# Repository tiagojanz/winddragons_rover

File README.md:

# WindDragons — Sistema de Telemetria e Controlo Náutico (Rover & Base Station)

Projeto de automação, navegação autónoma e telemetria para boias robóticas de regata (**Rovers**) e estação de comando com ecrã (**Base Station**), baseado na **Placa Carrier Universal Dual ESP32-C6** (**Master Lafvin LCD 1.47" IPS** + **Coprocessador ESP32-C6 DevKitC-1**).

---

## 🛰️ 1. Arquitetura Global do Sistema

```mermaid
flowchart LR
  subgraph CLOUD["☁️ WindDragons Cloud"]
    API["HTTPS REST API<br/>/api/circuits/station/telemetry"]
  end

  subgraph BASE["🎮 BASE STATION - Dual ESP32-C6"]
    BM["Master: Lafvin ESP32-C6<br/>• LCD 1.47 pol. ST7789 320x172<br/>• MicroSD /www/base/<br/>• Web Server WiFi STA e AP<br/>• Joystick Analógico + Botões<br/>• Coordenador OTA Dual"]
    BC["Slave: ESP32-C6 DevKitC-1<br/>• Rádio LoRa SX1278 433 MHz<br/>• Polling e Escuta Contínua<br/>• Telemetria da Frota 1..8"]
    BM <-->|"UART Inter-ESP 115200 bps<br/>TX:IO2 / RX:IO1"| BC
  end

  subgraph ROVER["🚤 ROVER / BOIA AUTÓNOMA - Dual ESP32-C6"]
    RM["Master: Lafvin ESP32-C6<br/>• LCD 1.47 pol. ST7789 + MicroSD<br/>• GPS Quectel LC29H UART1<br/>• Dashboard Web e OTA Dual<br/>• Joystick Local Opcional"]
    RC["Slave: ESP32-C6 DevKitC-1<br/>• Rádio LoRa SX1278 433 MHz<br/>• IMU 9-DOF GY-BNO055 em J_EXP<br/>• PWM: ESC, Leme, Guincho, Trinco<br/>• Sensores: Bateria 6S, Hall, Fim-Curso<br/>• Fita LEDs WS2812B Strobe"]
    RM <-->|"UART Inter-ESP 115200 bps<br/>TX:IO2 / RX:IO1"| RC
  end

  BM <-->|"WiFi HTTPS JSON"| API
  BC <-->|"LoRa 433 MHz<br/>BW 250kHz • SF7"| RC
```

---

## 🧭 2. Esquema de Ligação — Bússola & IMU 9-DOF (`GY-BNO055` em `J_EXP`)

O módulo **GY-BNO055** liga-se diretamente à ilha de expansão **`J_EXP` (2x03 pinos, passo 2.54 mm)** da PCB Carrier (ligada ao **Coprocessador ESP32-C6 DevKitC-1**).

```mermaid
flowchart LR
  subgraph J_EXP["📌 Conector J_EXP - PCB Carrier C6"]
    direction TB
    P1["Pino 1: IO1 - GPIO 1<br/>Coluna Esq. Topo"]
    P3["Pino 3: IO11 - GPIO 11<br/>Coluna Esq. Meio"]
    P5["Pino 5: GND<br/>Coluna Esq. Base"]
    P2["Pino 2: 3V3 - +3.3V_C6<br/>Coluna Dir. Topo"]
    P4["Pino 4: 5V<br/>Não ligar ao BNO055"]
    P6["Pino 6: GND<br/>Coluna Dir. Base"]
  end

  subgraph BNO["🧭 Módulo GY-BNO055 - I2C 0x28"]
    direction TB
    VIN["VIN - Alimentação 3.3V"]
    GND["GND - Terra Comum"]
    SCL["SCL / Rx - I2C Clock"]
    SDA["SDA / Tx - I2C Data"]
    ADD["ADD - Aberto = 0x28"]
    INT["INT / BOOT / REST - NC"]
  end

  P2 -->|"🔴 Fio Vermelho +3.3V"| VIN
  P5 -->|"⚫ Fio Preto GND"| GND
  P3 -->|"🟡 Fio Amarelo I2C SCL"| SCL
  P1 <-->|"🔵 Fio Azul/Verde I2C SDA"| SDA
```

### Disposição Física da Serigrafia `J_EXP` na PCB vs `GY-BNO055`

```text
       PCB CARRIER — ILHA J_EXP                     MÓDULO GY-BNO055
    ┌────────────────────────────┐               ┌────────────────────┐
    │     Col. Esq.    Col. Dir. │               │  [o] VIN     <────────── Pino 2 (3V3)
    │                            │               │  [o] GND     <────────── Pino 5 ou 6 (GND)
    │     [■] IO1      [●] 3V3   │ ──(Pinos 1,2) │  [o] SCL\Rx  <────────── Pino 3 (IO11)
    │     [●] IO11     [●] 5V    │ ──(Pinos 3,4) │  [o] SDA\Tx  <────────── Pino 1 (IO1)
    │     [●] GND      [●] GND   │ ──(Pinos 5,6) │  [o] ADD     (NC = 0x28)
    │         EXPANSION          │               │  [o] INT     (NC)
    └────────────────────────────┘               │  [o] BOOT    (NC)
                                                 │  [o] REST    (NC)
                                                 └────────────────────┘
```

| Pino no `GY-BNO055` | Pino em `J_EXP` (PCB) | GPIO ESP32-C6 (Slave) | Função / Notas |
| :--- | :--- | :--- | :--- |
| **`VIN`** | **`3V3`** (Pino 2 — Topo Direito) | `+3.3V_C6` | **Usar `3V3`** para manter níveis lógicos I2C a 3.3V puros |
| **`GND`** | **`GND`** (Pino 5 ou 6 — Base) | `GND` | Terra comum de referência |
| **`SCL \ Rx`** | **`IO11`** (Pino 3 — Meio Esquerdo) | `GPIO 11` | **I2C SCL** (Clock a 100 kHz com *clock stretching* ativo) |
| **`SDA \ Tx`** | **`IO1`** (Pino 1 — Topo Esquerdo) | `GPIO 1` | **I2C SDA** (Dados bidirecionais) |
| **`ADD` / `INT` / `BOOT` / `REST`** | *Não ligados (NC)* | — | Endereço I2C padrão `0x28` (deteção automática `0x28` / `0x29`) |

> [!IMPORTANT]
> **Pontes `PS0` e `PS1` no módulo GY-BNO055:** Certifique-se de que as duas pontes de solda **`PS0`** e **`PS1`** na placa azul do `GY-BNO055` estão **abertas (`LOW` / `0`)** para operar em modo **Standard I2C**.

---

## 🔌 3. Esquema Completo de Ligações — ROVER (Boia Autónoma)

```mermaid
flowchart TB
  subgraph MASTER["🖥️ MASTER: Lafvin ESP32-C6 - LCD 1.47 pol. IPS + MicroSD"]
    LCD["Ecrã ST7789 172x320<br/>MOSI:IO6 • SCLK:IO7 • CS:IO14<br/>DC:IO15 • RST:IO21 • BL:IO22"]
    SD["Leitor MicroSD Onboard<br/>CS:IO4 • MISO:IO5<br/>MOSI:IO6 • SCLK:IO7"]
    M_UART["UART Inter-ESP J1<br/>TX: IO2 Pad 4<br/>RX: IO1 Pad 5"]
    M_GPS["UART1 GPS J2<br/>TX: IO16 Pad 8<br/>RX: IO17 Pad 9"]
    M_JOY["Joystick Local J1<br/>VRx: IO3 Pad 3<br/>VRy: IO0 Pad 6"]
  end

  subgraph SLAVE["⚙️ SLAVE / COPROCESSADOR: ESP32-C6 DevKitC-1"]
    S_UART["UART Inter-ESP J3<br/>RX: GPIO 22 Pin 6<br/>TX: GPIO 13 Pin 13"]
    S_LORA["SPI Hardware FSPI<br/>NSS:IO6 • SCK:IO5 • MOSI:IO7<br/>MISO:IO4 • DIO0:IO0"]
    S_I2C["Barramento I2C J_EXP<br/>SDA: GPIO 1 IO1<br/>SCL: GPIO 11 IO11"]
    S_PWM["Controladores PWM 50 Hz<br/>ESC: GPIO 17 • RUD: GPIO 15<br/>WIN: GPIO 23 • RCK: GPIO 21"]
    S_SENS["Entradas de Sensores<br/>Bateria V: GPIO 2 • I: GPIO 3<br/>Fim Curso: GPIO 18 • Hall: GPIO 20<br/>LEDs Strobe: GPIO 19"]
  end

  GPS_MOD["🛰️ GPS Quectel LC29H<br/>115200 bps • 3.3V"]
  JOY_MOD["🕹️ Joystick Analógico<br/>Opcional no Rover"]
  M_GPS <-->|"TX:IO16 para R1 / RX:IO17 de T1"| GPS_MOD
  JOY_MOD --> M_JOY

  M_UART <-->|"115200 bps<br/>Verde IO2-IO22 • Amarelo IO13-IO1"| S_UART

  LORA_MOD["📡 Rádio LoRa Ra-02<br/>SX1278 433 MHz"]
  BNO_MOD["🧭 Bússola e IMU 9-DOF<br/>GY-BNO055 0x28"]
  ACT_MOD["⚡ Atuadores PWM<br/>• ESC Motor IO17<br/>• Servo Leme IO15<br/>• Servo Guincho IO23<br/>• Servo Cremalheira IO21"]
  ANCH_MOD["⚓ Sensores e Strobe<br/>• Power Module 6S IO2 e IO3<br/>• Microswitch Topo IO18<br/>• Sensor Hall DRV5032 IO20<br/>• Fita WS2812B 8 LEDs IO19"]

  S_LORA <--> LORA_MOD
  S_I2C <--> BNO_MOD
  S_PWM --> ACT_MOD
  S_SENS <--> ANCH_MOD
```

### Mapa da Barra Inferior de Conectores da PCB Carrier (`Dual_ESP_Carrier`)

```text
┌────────────────────────────────────────────────────────────────────────────────────────┐
│  BARRA INFERIOR DE ATUADORES E SENSORES (Passo 2.54 mm — Esquerda para a Direita)      │
├───────┬───────┬───────┬───────┬────────┬────────┬─────────┬─────────┬──────────────────┤
│  ESC  │  RUD  │  WIN  │  RCK  │  STRB  │ J_BATT │ J_LIMIT │ J_WATER │       HALL       │
│ (3p)  │ (3p)  │ (3p)  │ (3p)  │  (3p)  │  (3p)  │  (2p)   │  (2p)   │       (3p)       │
├───────┼───────┼───────┼───────┼────────┼────────┼─────────┼─────────┼──────────────────┤
│ 1:GND │ 1:GND │ 1:GND │ 1:GND │ 1:GND  │ 1:GND  │ 1:GND   │ 1:GND   │ 1:GND (Preto)    │
│ 2:+5V │ 2:+5V │ 2:+5V │ 2:+5V │ 2:+5V  │ 2:IO3  │ 2:IO18  │ 2:IO15  │ 2:+3V3_C6 (Verm) │
│ 3:IO17│ 3:IO15│ 3:IO23│ 3:IO21│ 3:IO19 │ 3:IO2  │ (Switch)│ (Água)  │ 3:IO20 (Amarelo) │
└───────┴───────┴───────┴───────┴────────┴────────┴─────────┴─────────┴──────────────────┘
```

### Tabela Completa de Pinos do Rover

#### A. Comunicação Entre Placas (Master Lafvin $\leftrightarrow$ Slave DevKitC-1)
| Sinal | Pino Master (Lafvin `J1`) | Pino Slave (DevKitC-1 `J3`) | Cor de Referência | Função |
| :--- | :--- | :--- | :--- | :--- |
| **Master TX $\rightarrow$ Slave RX** | `GPIO 2` (`J1` Pad 4 — Serigrafia `2`) | `GPIO 22` (`J3` Pin 6) | 🟢 Verde | Comandos, GPS, Config e OTA para o C6 |
| **Slave TX $\rightarrow$ Master RX** | `GPIO 1` (`J1` Pad 5 — Serigrafia `1`) | `GPIO 13` (`J3` Pin 13) | 🟡 Amarelo | Telemetria LoRa, Bateria, Âncora e Estados |
| **Terra Comum** | `GND` (`J1` Pad 8) | `GND` (`J3` Pin 14) | ⚫ Preto | Referência comum obrigatória |

#### B. Periféricos Ligados ao Coprocessador ESP32-C6 DevKitC-1 (Rover)
| Periférico / Conector PCB | Pino do Módulo | GPIO DevKitC-1 | Notas Técnicas |
| :--- | :--- | :--- | :--- |
| **LoRa SX1278 (`J3_LORA`)** | `NSS` / `SCK` / `MOSI` / `MISO` / `DIO0` | `IO6` / `IO5` / `IO7` / `IO4` / `IO0` | Alimentado por `+3V3_C6` dedicado (433.0 MHz) |
| **Bússola `GY-BNO055` (`J_EXP`)** | `SDA` (`Pino 1`) / `SCL` (`Pino 3`) | `GPIO 1` (`SDA`) / `GPIO 11` (`SCL`) | Alimentado em `J_EXP Pino 2 (3V3)` e `Pino 5/6 (GND)` |
| **ESC Motor (`ESC`)** | Sinal PWM (Pino 3) | `GPIO 17` | 50 Hz (`1000..2000 µs`, Neutro `1500 µs`) |
| **Servo do Leme (`RUD`)** | Sinal PWM (Pino 3) | `GPIO 15` | 50 Hz proporcional (`-100%` a `+100%`) |
| **Guincho da Âncora (`WIN`)** | Sinal PWM (Pino 3) | `GPIO 23` | Rotação contínua (`1800 µs` sobe, `1200 µs` desce, `1500 µs` para) |
| **Servo Cremalheira (`RCK`)** | Sinal PWM (Pino 3) | `GPIO 21` | Trinco mecânico (`0°` travado / `90°` queda livre) |
| **LEDs WS2812B Strobe (`STRB`)**| `DIN` (Pino 3) + `+5V_SERVO` + `GND` | `GPIO 19` | Fita/Anel NeoPixel 8 LEDs RGB (Strobe / Navegação / Bateria) |
| **Fim de Curso Âncora (`J_LIMIT`)**| Contacto NA (Pino 1 `GND`, Pino 2 `Sinal`) | `GPIO 18` | `INPUT_PULLUP` — fecha ao `GND` quando a âncora toca no topo |
| **Sensor Hall Tambor (`HALL`)** | `GND` (1), `+3V3_C6` (2), `OUT` (3) | `GPIO 20` | Sensor TI **DRV5032** (`INPUT_PULLUP`, interrupção `FALLING`) |
| **Power Module 6S (`J_BATT`)** | `GND` (1), `CURR` (2), `VOLT` (3) | `GPIO 2` (V) / `GPIO 3` (I) | Leitura ADC LiPo 6S (divisor `10.803`, `27.32 A/V`) |

#### C. Periféricos Ligados ao Master Lafvin ESP32-C6 (Rover)
| Periférico / Conector PCB | Pino do Módulo | GPIO Lafvin | Notas Técnicas |
| :--- | :--- | :--- | :--- |
| **GPS Quectel LC29H (`J6`)** | `VCC` (`3V3`), `GND`, `R1` (RX), `T1` (TX) | `GPIO 16` (TX) / `GPIO 17` (RX) | UART1 a **115200 bps** (`R1` liga a `IO16`, `T1` liga a `IO17`) |
| **Ecrã LCD 1.47" ST7789** | Integrado na placa Lafvin | `IO6, IO7, IO14, IO15, IO21, IO22` | Resolução `320x172` Landscape |
| **Leitor MicroSD (TF Card)** | Integrado na placa Lafvin | `CS=IO4`, `MISO=IO5`, `MOSI=IO6`, `SCK=IO7` | Armazena `/www/rover/`, `/config.json` e `/telemetry.csv` |
| **Joystick Físico (`JOY1`)** | `3V3`, `GND`, `VRx`, `VRy` | `GPIO 3` (X) / `GPIO 0` (Y) | Ativável/desativável na página `/config` |

---

## 🎮 4. Esquema Completo de Ligações — BASE STATION (Comando de Frota)

```mermaid
flowchart LR
  subgraph BASE_M["🖥️ BASE MASTER: Lafvin ESP32-C6"]
    B_LCD["Ecrã LCD 1.47 pol. ST7789<br/>Dashboard Frota, Regata e Rede"]
    B_SD["MicroSD Onboard CS:IO4<br/>/www/base/ + Registo de Missões"]
    B_JOY["Joystick Analógico PS5 J1<br/>Eixo X Leme: GPIO 3<br/>Eixo Y Motor: GPIO 0"]
    B_BTN["Botões Físicos<br/>BOOT Página: GPIO 9<br/>SW1/SW2/SW3: IO18 / IO19 / IO20"]
    B_UART["UART Inter-ESP<br/>TX: GPIO 2 • RX: GPIO 1"]
  end

  subgraph BASE_C["📡 BASE SLAVE: ESP32-C6 DevKitC-1"]
    BC_UART["UART Inter-ESP<br/>RX: GPIO 22 • TX: GPIO 13"]
    BC_LORA["Rádio LoRa SX1278 433 MHz<br/>NSS:IO6 • SCK:IO5 • MOSI:IO7<br/>MISO:IO4 • DIO0:IO0"]
  end

  B_UART <-->|"115200 bps<br/>Comandos e Telemetria Frota"| BC_UART
  BC_LORA <-->|"Antena 433 MHz"| AIR(("🌊 Rovers 1..8"))
```

---

## 🚀 5. Compilação e Pacotes de Atualização OTA Dual

Com o **PlatformIO** e **Python 3** instalados:

```bash
# 1. Gerar apenas os ficheiros Web comprimidos (.gz) para Rover e Base:
python3 scripts/build_web_assets.py

# 2. Compilar e empacotar o Firmware Completo do ROVER (C6 + Lafvin + Web):
python3 scripts/bundle_firmware.py
# -> Gera: dist/rover_firmware.zip

# 3. Compilar e empacotar o Firmware Completo da BASE STATION (C6 + Lafvin + Web):
python3 scripts/bundle_base_firmware.py
# -> Gera: dist/base_firmware.zip
```

> [!TIP]
> Para documentação detalhada de validação elétrica de bancada, separação dos domínios `+3V3` / `+3V3_C6` e especificações da régua destacável do sensor Hall DRV5032, consulte o ficheiro [`HARDWARE_PINOUT_MEMORY.md`](HARDWARE_PINOUT_MEMORY.md).

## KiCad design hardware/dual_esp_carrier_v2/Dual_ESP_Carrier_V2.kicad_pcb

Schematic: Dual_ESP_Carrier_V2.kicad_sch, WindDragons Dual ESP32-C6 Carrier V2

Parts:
C_ADS1, C_ADS2: 100nF; C_0805_2012Metric
C_BAT1: 22uF; C_0805_2012Metric
C_BIN: 22uF; C_0805_2012Metric
C_BOUT1, C_BOUT2: 22uF; C_0805_2012Metric
C_BST1, C_BST2: 100nF; C_0805_2012Metric
C_C6_EN, C_C6_VDD: 100nF; C_0805_2012Metric
C_CHGIN: 22uF; C_0805_2012Metric
C_F1, C_F2, C_F3, C_F4, C_F5, C_F6: 100nF; C_0805_2012Metric
C_HALL: 100nF; C_0805_2012Metric
C_LDO_IN: 22uF; C_0805_2012Metric
C_LDO_OUT: 22uF; C_0805_2012Metric
C_LORA: 100nF; C_0805_2012Metric
C_SRV: 22uF; C_0805_2012Metric
C_SYS1, C_SYS2: 22uF; C_0805_2012Metric
C_VIN: 100nF; C_0805_2012Metric
D_5V: GRN_5V; LED_0805_2012Metric
D_CHG: RED_CHG; LED_0805_2012Metric
D_LDO_5V: B5819W; D_SOD-123
D_LDO_USB: B5819W; D_SOD-123
D_SOL: B5819W; D_SOD-123
D_USB: B5819W; D_SOD-123
ESC: ESC; PinHeader_1x03_P2.54mm_Horizontal
F1: 1.5A_PTC; Fuse_1206_3216Metric
F_BAL: 1.5A_PTC; Fuse_1206_3216Metric
H1, H2, H3, H4: M3; MountingHole_3.2mm_M3
H_HALL: M3; MountingHole_3.2mm_M3
J1: ESP32-C6-LCD-1.47; PinHeader_1x09_P2.54mm_Horizontal
J2: ESP32-C6-LCD-1.47_B; PinHeader_1x09_P2.54mm_Horizontal
J6: GPS_LC29H_7PIN; PinHeader_1x07_P2.54mm_Horizontal
JOY1: PS5_JOYSTICK; Alps_RKJXV1224005
JP_2S_ADC: 2S_MON; SolderJumper-2_P1.3mm_Open_Pad1.0x1.5mm
J_BAL_MOT: LIPO_3S_6S_BAL; PinHeader_1x07_P2.54mm_Horizontal
J_IMU: GY_BNO055_I2C; JST_XH_S4B-XH-A_1x04_P2.50mm_Horizontal
J_LIMIT: ANCHOR LIMIT; PinHeader_1x02_P2.54mm_Vertical
J_LIPO_2S: 2S_LIPO_BAL; JST_XH_S3B-XH-A_1x03_P2.50mm_Horizontal
J_PWR_ESP: 5V_ESP_AUX; PinHeader_1x02_P2.54mm_Vertical
J_PWR_SRV: 5V_6V_BEC; PinHeader_1x02_P2.54mm_Vertical
J_SOLAR: SOLAR_5_6V; JST_XH_S2B-XH-A_1x02_P2.50mm_Horizontal
J_SW_EXT: EXT_SW; PinHeader_1x02_P2.54mm_Vertical
J_USBC: TYPE-C-31-M-12; USB_C_Receptacle_HRO_TYPE-C-31-M-12
J_WATER: WATER/ANC; PinHeader_1x02_P2.54mm_Vertical
J_WINCH_HUB: WINCH_HUB_6P; PinHeader_1x06_P2.54mm_Horizontal
J_WINCH_SUB: WINCH_6P_IN; PinHeader_1x06_P2.54mm_Vertical
L1: 2.2uH; L_Sunlord_MWSA0402S
L2: 4.7uH; L_Sunlord_MWSA0402S
Q_PROT: AO3401A; SOT-23
RCK: RACK; PinHeader_1x03_P2.54mm_Horizontal
RUD: RUDDER; PinHeader_1x03_P2.54mm_Horizontal
R_2S_BOT: 33k; R_0805_2012Metric
R_2S_TOP: 100k; R_0805_2012Metric
R_BAL: 10R; R_0805_2012Metric
R_C1B, R_C2T, R_C4T, R_C6T: 100k; R_0805_2012Metric
R_C1T, R_C2B: 51k; R_0805_2012Metric
R_C3B: 33k; R_0805_2012Metric
R_C3T: 120k; R_0805_2012Metric
R_C4B, R_C5B: 15k; R_0805_2012Metric
R_C5T: 110k; R_0805_2012Metric
R_C6B, R_C6_EN: 10k; R_0805_2012Metric
R_CC1, R_CC2: 5.1k; R_0603_1608Metric
R_CEN: 10k; R_0805_2012Metric
R_FB1: 110k; R_0805_2012Metric
R_FB2: 15k; R_0805_2012Metric
R_I2C_SCL, R_I2C_SDA: 10k; R_0805_2012Metric
R_IO8_PU: 10k; R_0805_2012Metric
R_ISET: 100k; R_0805_2012Metric
R_LED1: 1k; R_0805_2012Metric
R_LED2: 2.2k; R_0805_2012Metric
R_NTC: 51k; R_0805_2012Metric
R_QG: 100k; R_0805_2012Metric
R_SW_PD: 100k; R_0805_2012Metric
R_SW_PU: 10k; R_0805_2012Metric
R_UV: 120k; R_0805_2012Metric
R_VIN: 2R; R_0805_2012Metric
SRV_RCK: RACK_SRV; PinHeader_1x03_P2.54mm_Vertical
SRV_WIN: WINCH_SRV; PinHeader_1x03_P2.54mm_Vertical
STRB: WS2812B; PinHeader_1x03_P2.54mm_Horizontal
SW1: subir ancora; SKRKAEE020
SW2: MODE; SKRKAEE020
SW3: largar ancora; SKRKAEE020
SW4: BOOT; SKRKAEE020
SW_C6_BOOT, SW_C6_RST: SKRKAEE020; SW_Push_SPST_NO_Alps_SKRK
SW_PWR: PWR_ON_OFF; SW_SPDT_Shouhan_MSK12C02
U_ADS1, U_ADS2: ADS1115; MSOP-10_3x3mm_P0.5mm
U_BUCK: MT2492; SOT-23-6
U_C6: ESP32-C6-WROOM-1-N8; ESP32-C6-WROOM-1
U_CHG: IP2326; QFN-24-1EP_4x4mm_P0.5mm_EP2.6x2.6mm
U_HALL: DRV5032FADBZR; SOT-23
U_LDO: AMS1117-3.3; SOT-223-3_TabPin2
U_LORA: Ra-02; Ai-Thinker-Ra-01-LoRa
WIN: WINCH; PinHeader_1x03_P2.54mm_Horizontal

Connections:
/+3V3: J1.7, J6.7, JOY1.3 (Y_3V3), JOY1.6 (X_3V3)
/+3V3_C6: C_ADS1.1, C_ADS2.1, C_C6_VDD.1, C_LDO_OUT.1, C_LORA.1, J_IMU.2, J_WINCH_HUB.3, R_C6_EN.2, R_I2C_SCL.1, R_I2C_SDA.1, R_IO8_PU.2, U_ADS1.8 (VDD), U_ADS2.1 (ADDR), U_ADS2.8 (VDD), U_C6.2 (3V3), U_LDO.2 (VO), U_LORA.3 (VDD_3V3)
/+5V: C_BOUT1.1, C_BOUT2.1, D_LDO_5V.2 (A), J1.9, J_PWR_ESP.2, L2.2, R_FB1.1, R_LED2.1
/+5V_SERVO: ESC.2, J_PWR_SRV.2, J_WINCH_HUB.2, RCK.2, RUD.2, STRB.2, WIN.2
/ADC_2S_DIV: JP_2S_ADC.1, R_2S_BOT.2, R_2S_TOP.2
/ADC_C1: C_F1.1, R_C1B.1, R_C1T.2, U_ADS1.7 (AIN3)
/ADC_C2: C_F2.1, R_C2B.1, R_C2T.2, U_ADS1.6 (AIN2)
/ADC_C3: C_F3.1, R_C3B.1, R_C3T.2, U_ADS1.5 (AIN1)
/ADC_C4: C_F4.1, R_C4B.1, R_C4T.2, U_ADS1.4 (AIN0)
/ADC_C5: C_F5.1, R_C5B.1, R_C5T.2, U_ADS2.5 (AIN1)
/ADC_C6: C_F6.1, R_C6B.1, R_C6T.2, U_ADS2.4 (AIN0)
/ANCHOR_HALL: J_WINCH_HUB.4, U_C6.18 (IO20)
/ANCHOR_LIMIT: J_LIMIT.2, U_C6.16 (IO18)
/BAL_C1: J_BAL_MOT.2, R_C1T.1
/BAL_C2: J_BAL_MOT.3, R_C2T.1
/BAL_C3: J_BAL_MOT.4, R_C3T.1
/BAL_C4: J_BAL_MOT.5, R_C4T.1
/BAL_C5: J_BAL_MOT.6, R_C5T.1
/BAL_C6: J_BAL_MOT.7, R_C6T.1
/BAL_GND: F_BAL.1, J_BAL_MOT.1
/BATT_VOLT: JP_2S_ADC.2, U_C6.27 (IO2)
/BUCK_BST: C_BST2.1, U_BUCK.1 (BST)
/BUCK_EN: R_SW_PD.2, R_SW_PU.2, U_BUCK.4 (EN)
/BUCK_EN_SW: J_SW_EXT.2, R_2S_TOP.1, R_SW_PU.1, SW_PWR.2 (COM)
/BUCK_FB: R_FB1.2, R_FB2.1, U_BUCK.3 (FB)
/BUCK_LX: C_BST2.2, L2.1, U_BUCK.6 (LX)
/C6_BOOT: SW_C6_BOOT.2, U_C6.15 (IO9/BOOT)
/C6_EN: C_C6_EN.1, R_C6_EN.1, SW_C6_RST.2, U_C6.3 (EN)
/C6_IO8: R_IO8_PU.1, U_C6.10 (IO8)
/CHG_BST: C_BST1.2, U_CHG.14 (BST)
/CHG_EN: R_CEN.2, U_CHG.12 (EN)
/CHG_ISET: R_ISET.1, U_CHG.11 (ISET)
/CHG_LED: R_LED1.1, U_CHG.6 (LED)
/CHG_LED_K: D_CHG.2 (A), R_LED1.2
/CHG_LX: C_BST1.1, L1.2, U_CHG.15 (LX1), U_CHG.16 (LX2), U_CHG.17 (LX3)
/CHG_NTC: R_NTC.1, U_CHG.4 (NTC)
/CHG_UV: R_UV.1, U_CHG.8 (VSET)
/CHG_VBATM: R_BAL.1, U_CHG.23 (VBATM)
/CHG_VIN: C_VIN.1, R_VIN.2, U_CHG.13 (VIN)
/CHG_VSYS: C_SYS1.1, C_SYS2.1, U_CHG.19 (VSYS1), U_CHG.20 (VSYS2)
/EXP_IO1: J_IMU.3, R_I2C_SDA.2, U_ADS1.9 (SDA), U_ADS2.9 (SDA), U_C6.9 (IO1)
/EXP_IO11: J_IMU.4, R_I2C_SCL.2, U_ADS1.10 (SCL), U_ADS2.10 (SCL), U_C6.12 (IO11)
/GND: C_ADS1.2, C_ADS2.2, C_BAT1.2, C_BIN.2, C_BOUT1.2, C_BOUT2.2, C_C6_EN.2, C_C6_VDD.2, C_CHGIN.2, C_F1.2, C_F2.2, C_F3.2, C_F4.2, C_F5.2, C_F6.2, C_LDO_IN.2, C_LDO_OUT.2, C_LORA.2, C_SYS1.2, C_SYS2.2, C_VIN.2, D_5V.1 (K), D_CHG.1 (K), ESC.1, F_BAL.2, J1.8, J6.6, JOY1.1 (Y_GND), JOY1.4 (X_GND), JOY1.7 (SW_A1), JOY1.11 (SH1), JOY1.12 (SH2), JOY1.13 (SH3), JOY1.14 (SH4), J_IMU.1, J_LIMIT.1, J_LIPO_2S.1, J_PWR_ESP.1, J_PWR_SRV.1, J_SOLAR.1, J_USBC.A1 (GND_A1), J_USBC.A12 (GND_A12), J_USBC.B1 (GND_B1), J_USBC.B12 (GND_B12), J_USBC.SH (SHIELD), J_WATER.1, J_WINCH_HUB.1, RCK.1, RUD.1, R_2S_BOT.1, R_C1B.2, R_C2B.2, R_C3B.2, R_C4B.2, R_C5B.2, R_C6B.2, R_CC1.1, R_CC2.1, R_FB2.2, R_ISET.2, R_NTC.2, R_QG.1, R_SW_PD.1, R_UV.2, STRB.1, SW1.2, SW2.2, SW3.2, SW4.2, SW_C6_BOOT.1, SW_C6_RST.1, SW_PWR.SH, U_ADS1.1 (ADDR), U_ADS1.3 (GND), U_ADS2.3 (GND), U_ADS2.6 (AIN2), U_ADS2.7 (AIN3), U_BUCK.2 (GND), U_C6.1 (GND), U_C6.28 (GND28), U_C6.29 (EPAD), U_CHG.18 (GND18), U_CHG.24 (GND24), U_CHG.25 (EPAD), U_LDO.1 (GND), U_LORA.1 (GND), U_LORA.2 (GND2), U_LORA.9 (GND9), U_LORA.16 (GND16), WIN.1
/GPS_RX: J2.8, J6.4
/GPS_TX: J2.9, J6.5
/HALL_GND: C_HALL.1, C_SRV.2, J_WINCH_SUB.1, SRV_RCK.1, SRV_WIN.1, U_HALL.3 (GND)
/HALL_OUT: J_WINCH_SUB.4, U_HALL.2 (OUT)
/HALL_VCC: C_HALL.2, J_WINCH_SUB.3, U_HALL.1 (VCC)
/INTER_RX_S2M: J1.5, U_C6.26 (IO3)
/INTER_TX_M2S: J1.4, U_C6.20 (IO22)
/IO4_FREE: J1.2
/IO5_FREE: J1.1
/IO9_BOOT: J2.1, SW4.1
/IO12_FREE: J2.6
/IO13_FREE: J2.7
/IO18_UP: J2.2, SW1.1
/IO19_MODE: J2.3, SW2.1
/IO20_DN: J2.4, SW3.1
/JOY_SW: J2.5, JOY1.10 (SW_B2)
/JOY_X: J1.3, JOY1.5 (X_WIPER)
/JOY_Y: J1.6, JOY1.2 (Y_WIPER)
/LDO_VIN: C_LDO_IN.1, D_LDO_5V.1 (K), D_LDO_USB.1 (K), U_LDO.3 (VI)
/LED_5V_A: D_5V.2 (A), R_LED2.2
/LORA_DIO0: U_C6.8 (IO0), U_LORA.5 (DIO0)
/LORA_MISO: U_C6.4 (IO4), U_LORA.13 (MISO)
/LORA_MOSI: U_C6.7 (IO7), U_LORA.14 (MOSI)
/LORA_NSS: U_C6.6 (IO6), U_LORA.15 (~NSS)
/LORA_SCK: U_C6.5 (IO5), U_LORA.12 (SCK)
/Q_GATE: Q_PROT.1 (G), R_QG.2
/SERVO_ESC: ESC.3, U_C6.24 (RXD0)
/SERVO_RACK: J_WINCH_HUB.6, RCK.3, U_C6.19 (IO21)
/SERVO_RUDDER: RUD.3, U_C6.23 (IO15)
/SERVO_WINCH: J_WINCH_HUB.5, U_C6.21 (IO23), WIN.3
/STROBE_DIN: STRB.3, U_C6.17 (IO19)
/SUB_5V: C_SRV.1, J_WINCH_SUB.2, SRV_RCK.2, SRV_WIN.2
/SUB_RCK: J_WINCH_SUB.6, SRV_RCK.3
/SUB_WIN: J_WINCH_SUB.5, SRV_WIN.3
/USB_CC1: J_USBC.A5 (CC1), R_CC1.2
/USB_CC2: J_USBC.B5 (CC2), R_CC2.2
/USB_DN: J_USBC.A7 (DN1), J_USBC.B7 (DN2), U_C6.13 (IO12/DN)
/USB_DP: J_USBC.A6 (DP1), J_USBC.B6 (DP2), U_C6.14 (IO13/DP)
/VBAT_2S: C_BAT1.1, F1.1, J_LIPO_2S.3, U_CHG.21 (BAT1), U_CHG.22 (BAT2)
/VBAT_FUSED: F1.2, Q_PROT.3 (S)
/VBAT_MID: J_LIPO_2S.2, R_BAL.2
/VBAT_PROT: C_BIN.1, J_SW_EXT.1, Q_PROT.2 (D), SW_PWR.3 (ON), U_BUCK.5 (VIN)
/VBUS_USB: D_LDO_USB.2 (A), D_USB.2 (A), J_USBC.A4 (VBUS_A4), J_USBC.A9 (VBUS_A9), J_USBC.B4 (VBUS_B4), J_USBC.B9 (VBUS_B9)
/VIN_CHG: C_CHGIN.1, D_SOL.1 (K), D_USB.1 (K), L1.1, R_CEN.1, R_VIN.1
/VSOLAR_IN: D_SOL.2 (A), J_SOLAR.2
/WATER_SENS: J_WATER.2, U_C6.11 (IO10)

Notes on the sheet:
USB-C Native JTAG + 5.1k CC + Dual-OR Schottky + IP2326 Boost-Balance Charger -> JST-XH 2S
Factory-Mounted SX1278 Ra-02 (IPEX/U.FL, SPI), Back GNSS UART Port (J6) & Left-Edge I2C IMU Port (J_IMU)
5. MOTOR LIPO 3S-6S CELL MONITOR (2x ADS1115 16-BIT I2C)
ST7789 IPS + TF MicroSD (SPI)
WAVESHARE ESP32-C6-LCD-1.47
2. ONBOARD ALPS RKJXV122400R 3D JOYSTICK (JOY1)
USB-C + 5V Buck Schottky OR -> AMS1117-3.3 -> Onboard C6 (RF Keepout, Native USB JTAG, BOOT/RST)
J_BAL_MOT 90-deg Input + F_BAL 1.5A PTC + 6x RC Dividers (GAIN_ONE) + ADS1115 (0x48 & 0x49) + I2C Pull-Ups
9. M3 MOUNTING HOLES
Inter-ESP UART: TX=IO2, RX=IO1
Dual 1x09 Master Headers (J1 Left / J2 Right) & 4x SKRKAEE020 Navigation/Boot Pushbuttons
1.5A PTC + AO3401A Reverse-Polarity PMOS + Parallel Power Switches + MT2492 Buck + Optional 2S ADC
BREAKAWAY WINCH + HALL SUB-BOARD
Diagonal Tact Switch: 7-9 & 8-10 shorted internally
7. 2S BATTERY PROTECTION, POWER SWITCH & MT2492 5.0V 2A BUCK
Dual 10k-B Potentiometers (GPIO3/GPIO0) & Diagonal Center-Push Tactile Switch (GPIO23)
3. ONBOARD AI-THINKER RA-02 LORA 433MHz, LC29H GNSS & GY-BNO055 IMU
6. USB-C (JTAG + 5V), SOLAR INPUT & IP2326 2S BALANCE CHARGER
4x Corner M3 (H1-H4) + Breakaway Hall Probe M3 (H_HALL)
8. RC SERVOS (5V BEC), SENSORS & BREAKAWAY WINCH/HALL SUB-BOARD
4. ONBOARD ESP32-C6-WROOM-1-N8 SLAVE MCU & DUAL-OR 3.3V LDO
Isolated Servo BEC Rail + Actuators + Water/Limit + 6P Winch Hub <-> Breakaway Hall + 2 Servos
1. WAVESHARE ESP32-C6-LCD-1.47 MASTER & UI BUTTONS

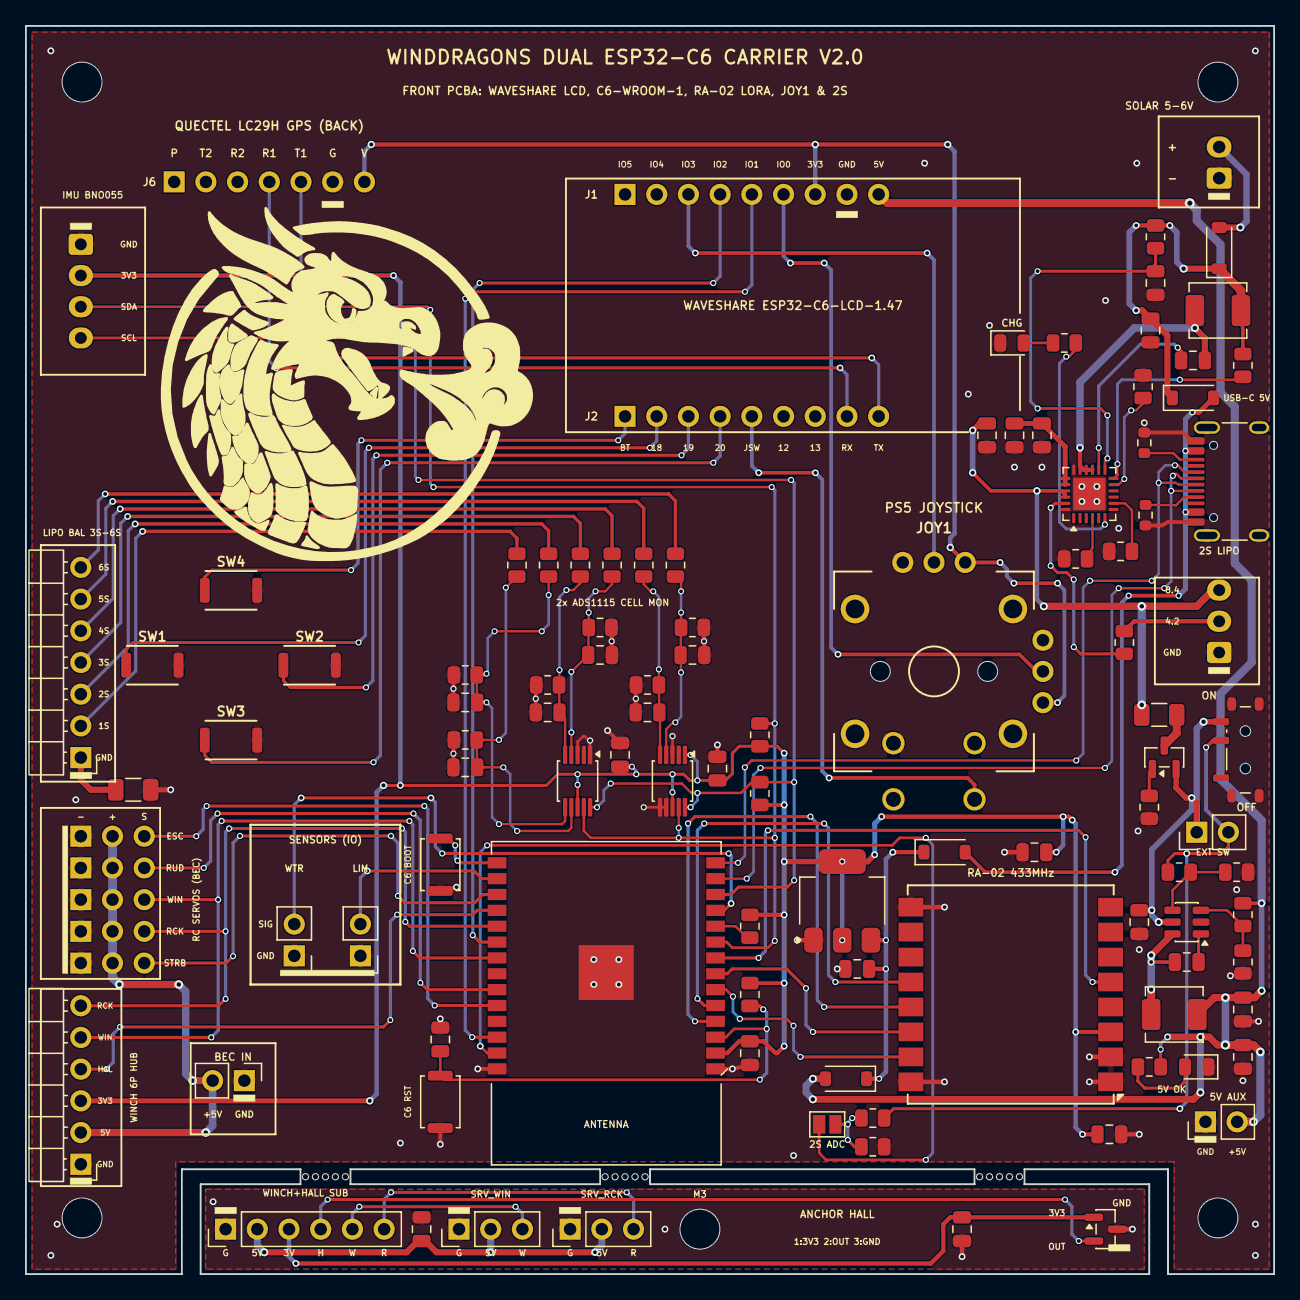
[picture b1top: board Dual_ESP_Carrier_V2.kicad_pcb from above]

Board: 2 copper layers, 100.0 x 100.0 mm, 128 parts (1 on the bottom side), 85 nets.

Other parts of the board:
STAMP1, STAMP2, STAMP3, STAMP4, STAMP5, STAMP6, STAMP7, STAMP8, STAMP9, STAMP10, STAMP11, STAMP12, STAMP13, STAMP14, STAMP15: MountingHole_0.5mm

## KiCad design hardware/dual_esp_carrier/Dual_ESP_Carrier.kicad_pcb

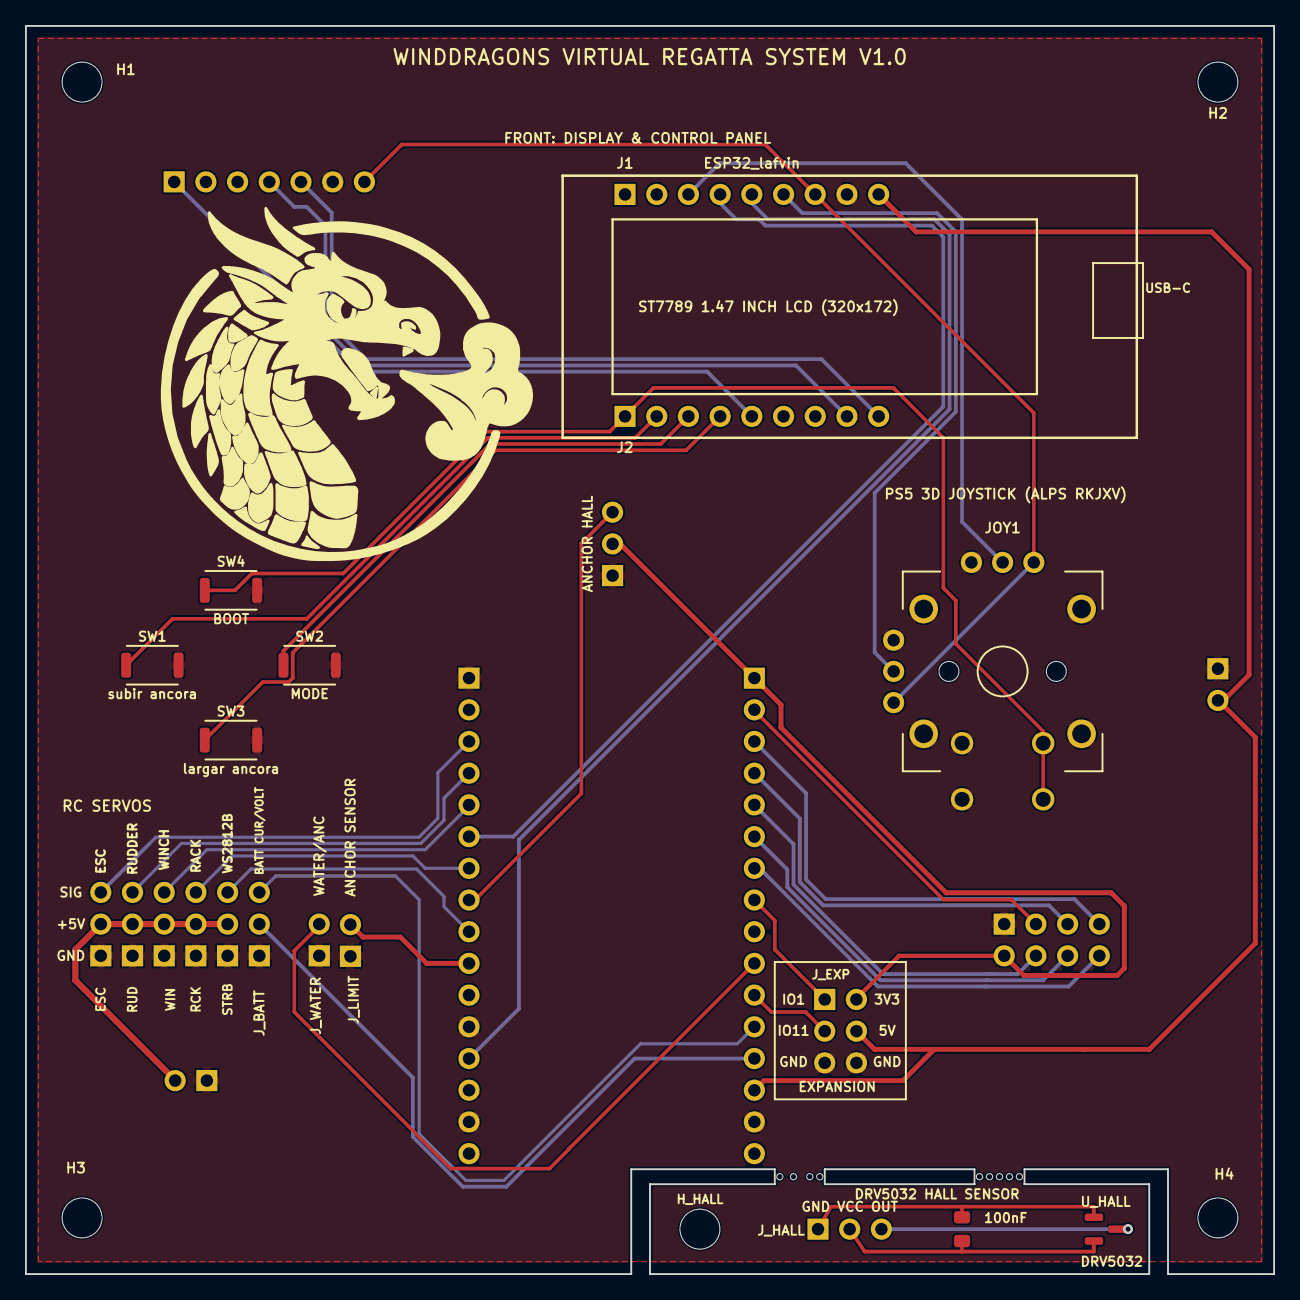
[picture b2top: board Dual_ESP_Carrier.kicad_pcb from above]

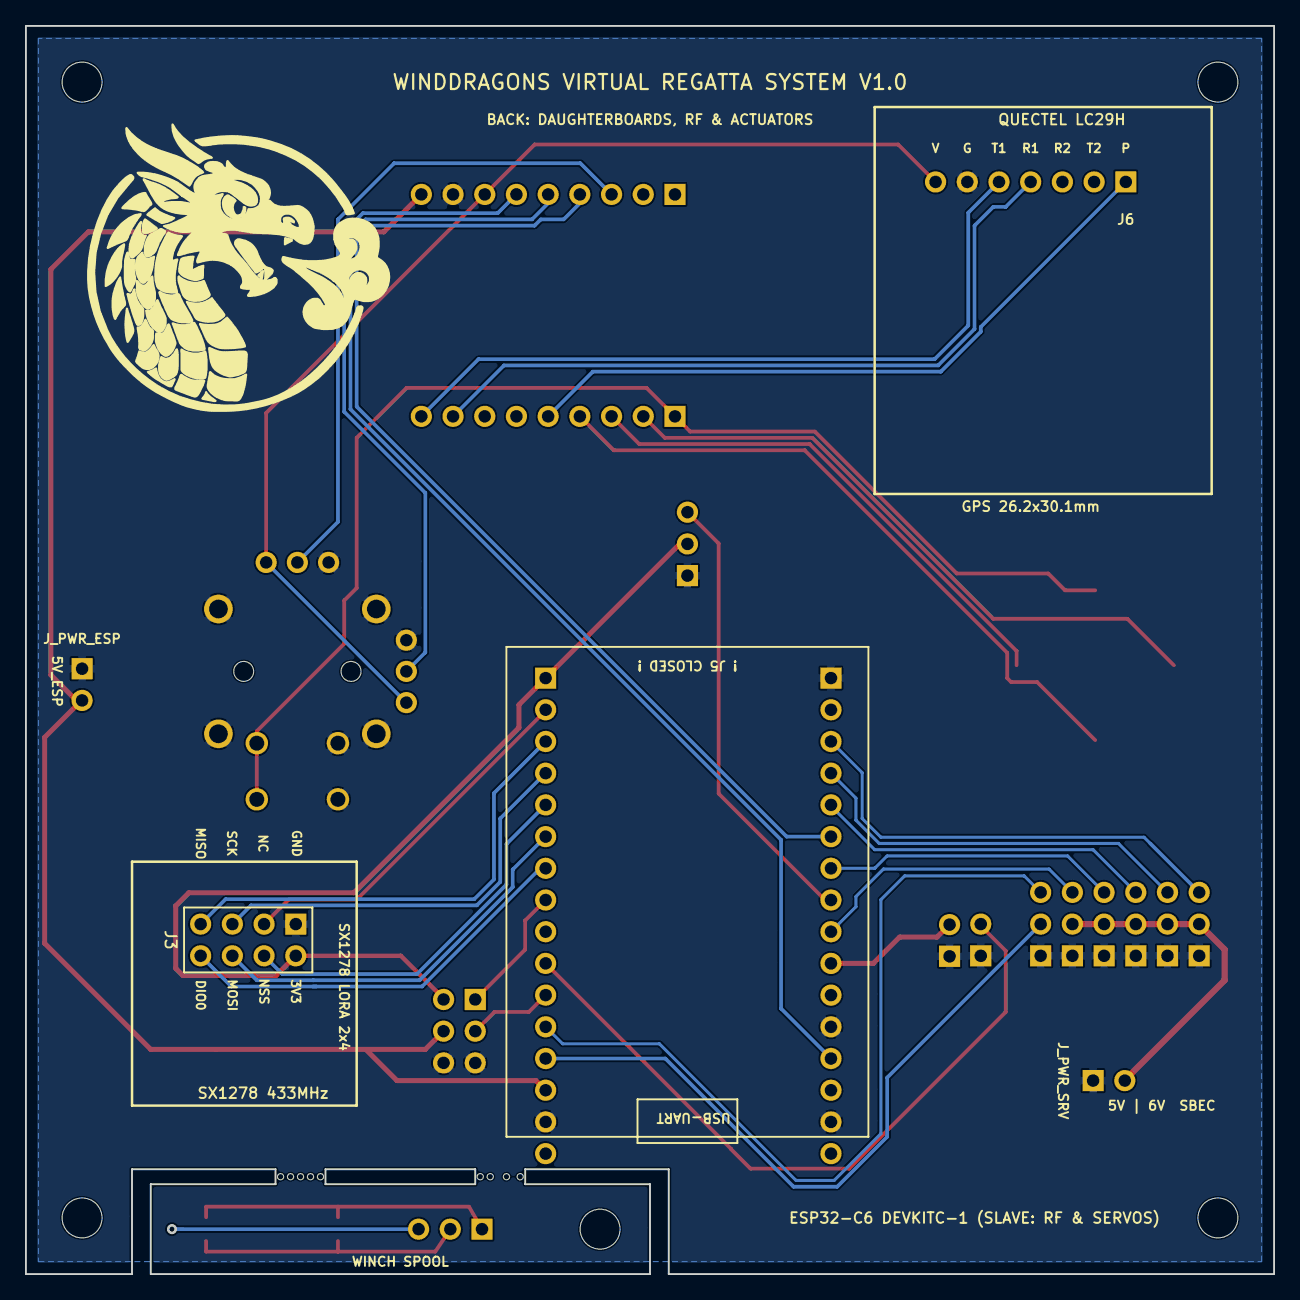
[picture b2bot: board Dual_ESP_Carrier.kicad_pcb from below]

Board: 2 copper layers, 100.0 x 100.0 mm, 40 parts (6 on the bottom side), 37 nets.

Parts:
C_HALL: 100nF; C_0805_2012Metric
ESC: ESC; PinHeader_1x03_P2.54mm_Vertical
H1, H2, H3, H4: MountingHole_3.2mm_M3
HALL: ANCHOR HALL; PinHeader_1x03_P2.54mm_Vertical
H_HALL: M3_MOUNT; MountingHole_3.2mm_M3
J1: ESP32_lafvin; PinHeader_1x09_P2.54mm_Horizontal
J2: ESP32_B_LANDSCAPE; PinHeader_1x09_P2.54mm_Horizontal
J3: SX1278_LORA_2x4; PinHeader_2x04_P2.54mm_Vertical
J6: GPS_LC29H_7PIN; PinHeader_1x07_P2.54mm_Horizontal
JOY1: PS5_JOYSTICK; Alps_RKJXV1224005
J_BATT: BATT CUR/VOLT; PinHeader_1x03_P2.54mm_Vertical
J_DK_L: PinHeader_1x16_P2.54mm_Vertical
J_DK_R: PinHeader_1x16_P2.54mm_Vertical
J_EXP: EXPANSION; PinHeader_2x03_P2.54mm_Vertical
J_HALL: GND_VCC_OUT; PinHeader_1x03_P2.54mm_Horizontal
J_LIMIT: ANCHOR SENSOR; PinHeader_1x02_P2.54mm_Vertical
J_PWR_ESP: 5V_ESP; PinHeader_1x02_P2.54mm_Vertical
J_PWR_SRV: 5V | 6V SBEC; PinHeader_1x02_P2.54mm_Vertical
J_WATER: WATER/ANC; PinHeader_1x02_P2.54mm_Vertical
RCK: RACK; PinHeader_1x03_P2.54mm_Vertical
RUD: RUDDER; PinHeader_1x03_P2.54mm_Vertical
STAMP: MountingHole_0.5mm
STAMP#2, STAMP#3, STAMP#4, STAMP#5, STAMP#6, STAMP#7, STAMP#8, STAMP#9: MountingHole_0.5mm
STRB: WS2812B; PinHeader_1x03_P2.54mm_Vertical
SW1: subir ancora; SKRKAEE020
SW2: MODE; SKRKAEE020
SW3: largar ancora; SKRKAEE020
SW4: BOOT; SKRKAEE020
U_HALL: DRV5032; SOT-23
WIN: WINCH; PinHeader_1x03_P2.54mm_Vertical

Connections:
/+3V3: J1.7, J6.7, JOY1.3, JOY1.6
/+3V3_C6: HALL.2, J3.2, J_DK_L.1, J_EXP.2
/+5V: J1.9, J_DK_L.14, J_EXP.4, J_PWR_ESP.2
/+5V_SERVO: ESC.2, J_PWR_SRV.2, RCK.2, RUD.2, STRB.2, WIN.2
/ANCHOR_HALL: HALL.3, J_DK_R.8
/ANCHOR_LIMIT: J_DK_R.10, J_LIMIT.2
/BATT_CURR: J_BATT.2, J_DK_L.13
/BATT_VOLT: J_BATT.3, J_DK_L.12
/EXP_IO1: J_DK_L.8, J_EXP.1
/EXP_IO11: J_DK_L.11, J_EXP.3
/GND: ESC.1, HALL.1, J1.8, J3.1, J6.6, JOY1.1, JOY1.4, JOY1.7, JOY1.8, JOY1.11, JOY1.12, JOY1.13, JOY1.14, J_BATT.1, J_DK_L.15, J_DK_R.1, J_DK_R.12, J_DK_R.15, J_EXP.5, J_EXP.6, J_LIMIT.1, J_PWR_ESP.1, J_PWR_SRV.1, J_WATER.1, RCK.1, RUD.1, STRB.1, SW1.2, SW2.2, SW3.2, SW4.2, WIN.1
/GPS_PPS: J2.5, J6.1
/GPS_RX: J2.8, J6.4
/GPS_TX: J2.9, J6.5
/HALL_GND: C_HALL.2, J_HALL.1, U_HALL.1
/HALL_OUT: J_HALL.3, U_HALL.3
/HALL_VCC: C_HALL.1, J_HALL.2, U_HALL.2
/INTER_RX_S2M: J1.5, J_DK_R.13
/INTER_TX_M2S: J1.4, J_DK_R.6
/IO9_BOOT: J2.1, JOY1.9, JOY1.10, SW4.1
/IO18_UP: J2.2, SW1.1
/IO19_MODE: J2.3, SW2.1
/IO20_DN: J2.4, SW3.1
/JOY_X: J1.3, JOY1.5
/JOY_Y: J1.6, JOY1.2
/LORA_DIO0: J3.8, J_DK_L.7
/LORA_MISO: J3.7, J_DK_L.3
/LORA_MOSI: J3.6, J_DK_L.6
/LORA_NSS: J3.4, J_DK_L.5
/LORA_RST: J3.3, J_DK_L.2
/LORA_SCK: J3.5, J_DK_L.4
/SERVO_ESC: ESC.3, J_DK_R.3
/SERVO_RACK: J_DK_R.7, RCK.3
/SERVO_RUDDER: J_DK_R.4, RUD.3
/SERVO_WINCH: J_DK_R.5, WIN.3
/STROBE_DIN: J_DK_R.9, STRB.3
/WATER_SENS: J_DK_L.10, J_WATER.2

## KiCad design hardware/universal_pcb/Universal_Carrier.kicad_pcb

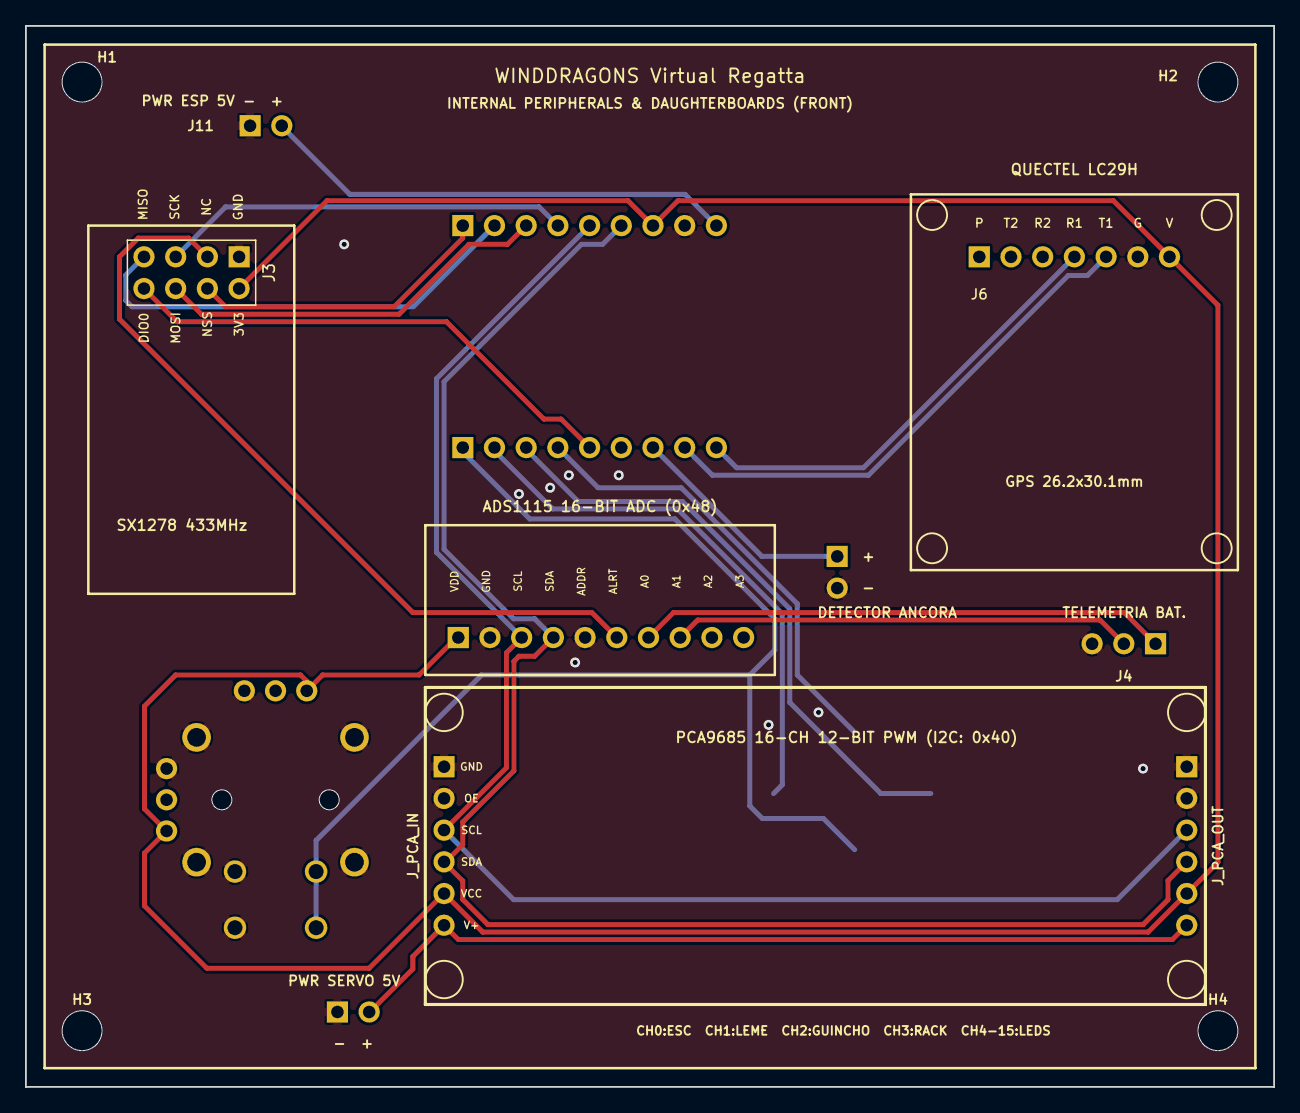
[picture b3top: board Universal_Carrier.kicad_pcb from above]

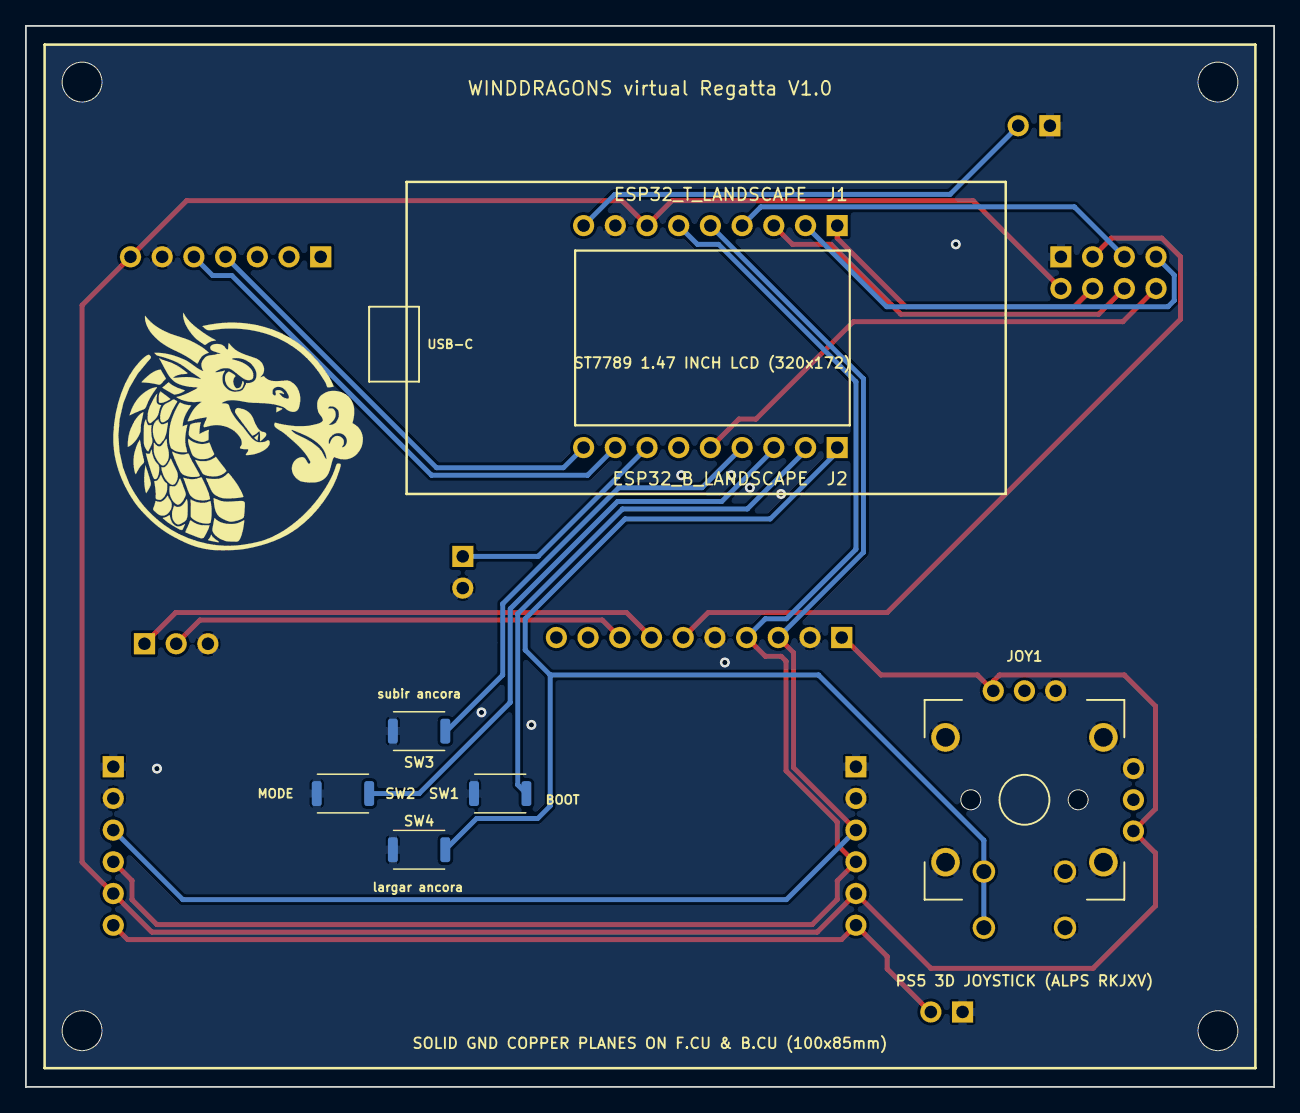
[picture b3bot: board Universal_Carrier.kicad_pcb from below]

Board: 2 copper layers, 100.0 x 85.0 mm, 21 parts (8 on the bottom side), 21 nets.

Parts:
H1, H2, H3, H4: MountingHole; MountingHole_3.2mm_M3
J1: ESP32_T_LANDSCAPE; PinHeader_1x09_P2.54mm_Horizontal
J2: ESP32_B_LANDSCAPE; PinHeader_1x09_P2.54mm_Horizontal
J3: SX1278_LORA_2x4; PinHeader_2x04_P2.54mm_Vertical
J4: BATT_APM; PinHeader_1x03_P2.54mm_Horizontal
J5: DETECTOR_ANCORA; PinHeader_1x02_P2.54mm_Vertical
J6: GPS_LC29H_7PIN; PinHeader_1x07_P2.54mm_Horizontal
J11: PWR_ESP_5V; PinHeader_1x02_P2.54mm_Horizontal
J12: PWR_SERVO_5V; PinHeader_1x02_P2.54mm_Horizontal
JOY1: PS5_JOYSTICK; Alps_RKJXV1224005
J_ADS: ADS1115_ADC; PinHeader_1x10_P2.54mm_Horizontal
J_PCA_IN: PCA9685_IN; PinHeader_1x06_P2.54mm_Vertical
J_PCA_OUT: PCA9685_OUT; PinHeader_1x06_P2.54mm_Vertical
LOGO1: WindDragons_Logo; WindDragons_Logo_20mm
SW1: subir ancora; SKRKAEE020
SW2: MODE; SKRKAEE020
SW3: largar ancora; SKRKAEE020
SW4: BOOT; SKRKAEE020

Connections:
/+3V3: J1.7, J3.2, J6.7, JOY1.3, JOY1.6, J_ADS.1, J_PCA_IN.5, J_PCA_OUT.5
/+5V: J1.9, J11.2
/+5V_SERVO: J12.2, J_PCA_IN.6, J_PCA_OUT.6
/BATT_CURR_APM: J4.2, J_ADS.8
/BATT_VOLT_APM: J4.1, J_ADS.7
/GND: J1.8, J3.1, J4.3, J5.2, J6.6, J11.1, J12.1, JOY1.1, JOY1.4, JOY1.7, JOY1.8, JOY1.11, JOY1.12, JOY1.13, JOY1.14, J_ADS.2, J_ADS.5, J_PCA_IN.1, J_PCA_IN.2, J_PCA_OUT.1, J_PCA_OUT.2, SW1.2, SW2.2, SW3.2, SW4.2
/I2C_SCL: J1.5, J_ADS.3, J_PCA_IN.3, J_PCA_OUT.3
/I2C_SDA: J1.6, J_ADS.4, J_PCA_IN.4, J_PCA_OUT.4
/IO2_SCK: J1.4, J3.5
/IO3_MOSI: J1.3, J3.6
/IO4_MISO: J1.2, J3.7
/IO5_NSS: J1.1, J3.4
/IO9_BOOT: J2.1, JOY1.9, JOY1.10, SW4.1
/IO13_ANCORA_DET: J2.7, J5.1
/IO16_GPS_RX: J2.8, J6.5
/IO17_GPS_TX: J2.9, J6.4
/IO18_UP: J2.2, SW1.1
/IO19_MODE: J2.3, SW2.1
/IO20_DN: J2.4, SW3.1
/IO23_LORA_DIO0: J2.5, J3.8
/NC: J3.3, J_ADS.6
